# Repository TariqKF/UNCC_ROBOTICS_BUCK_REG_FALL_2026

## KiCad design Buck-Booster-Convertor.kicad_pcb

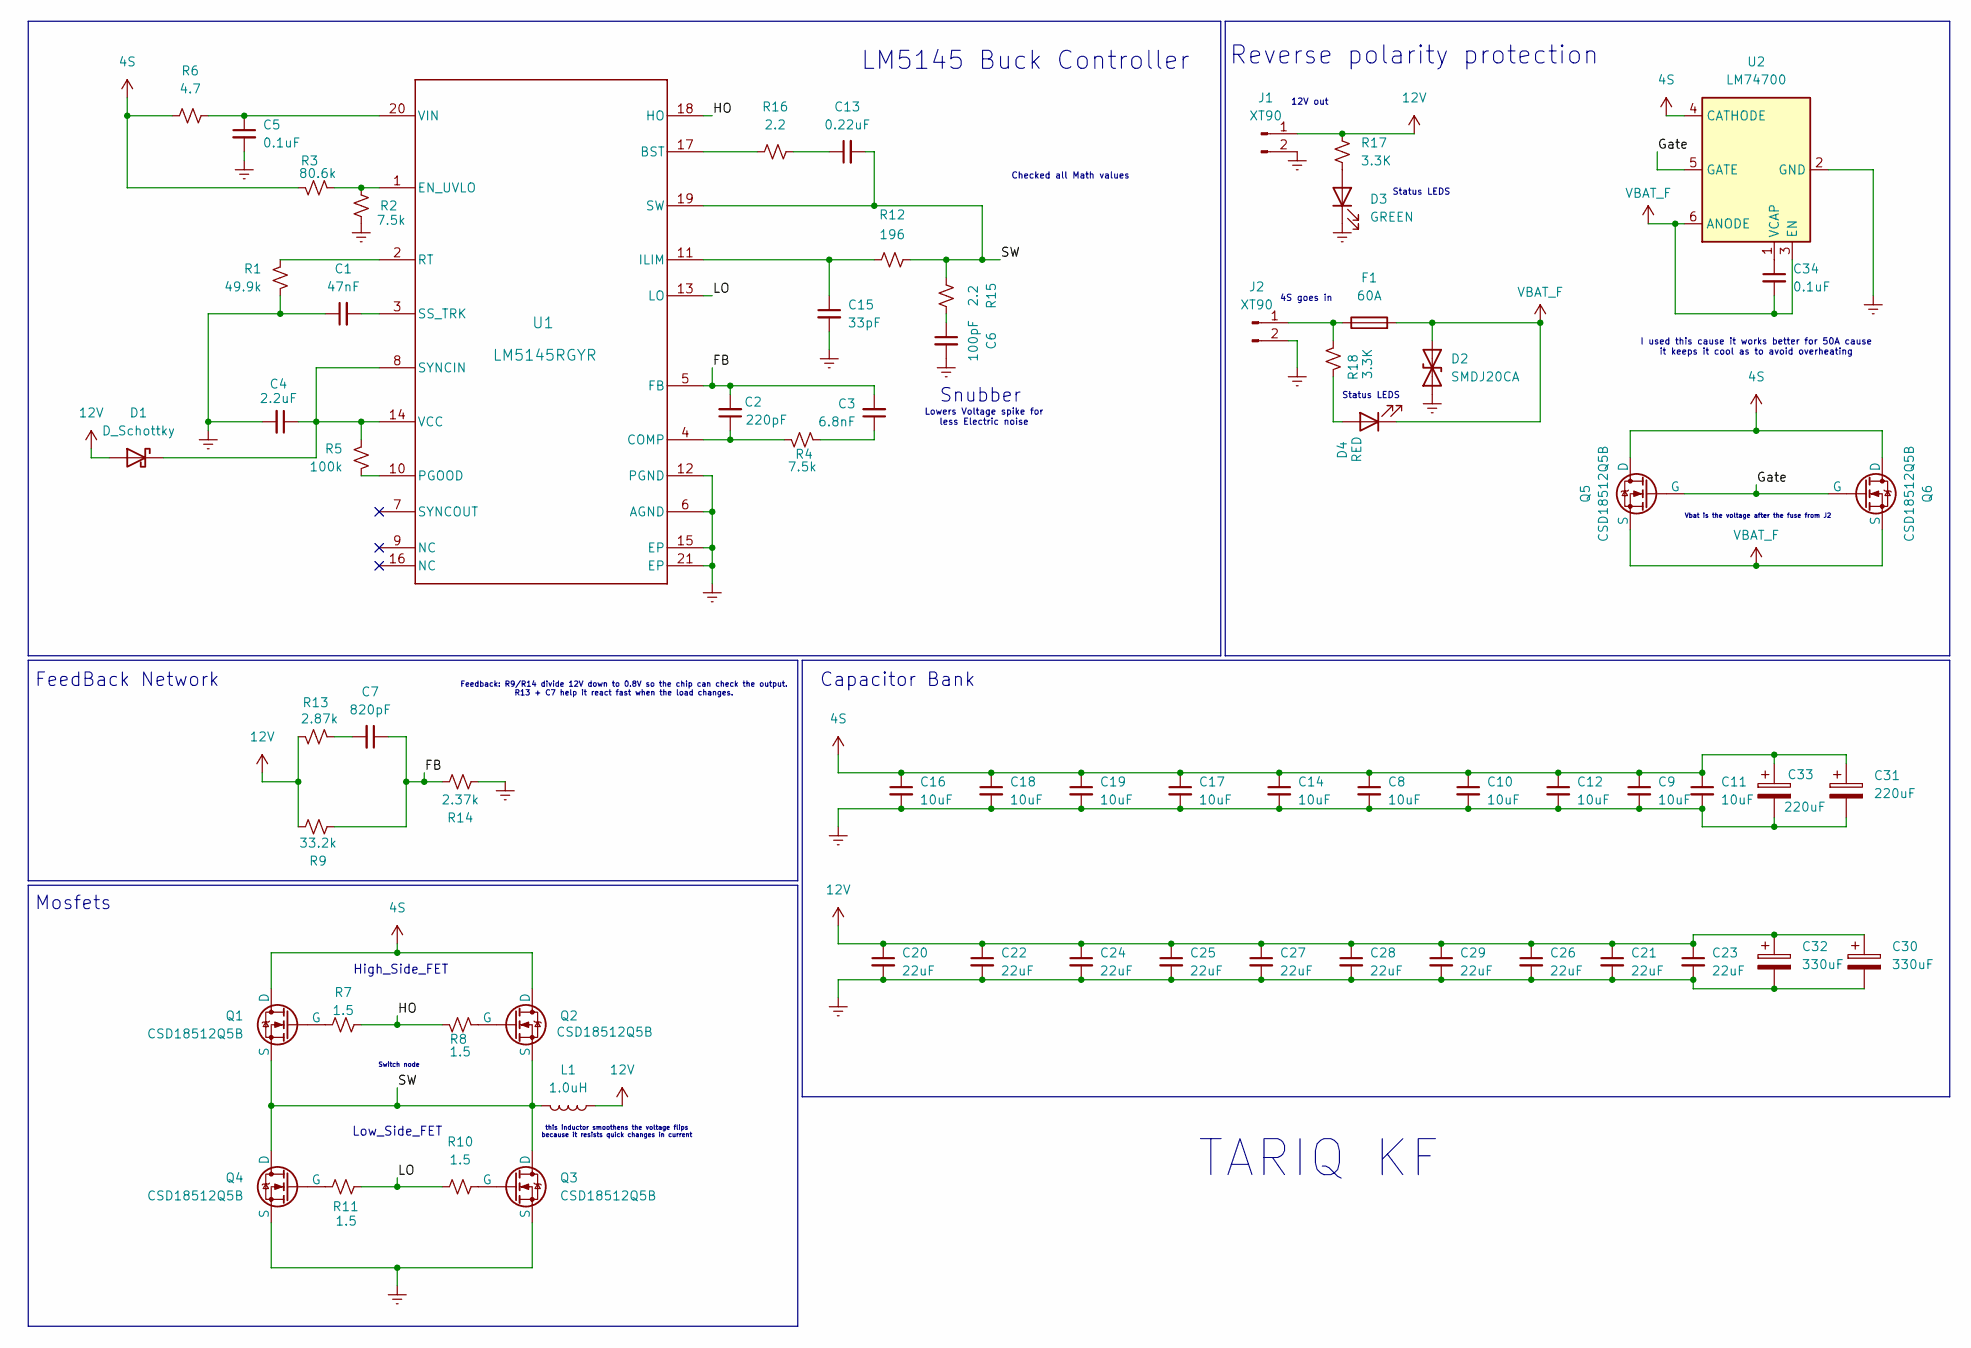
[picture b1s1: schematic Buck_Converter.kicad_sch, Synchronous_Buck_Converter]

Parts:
C1: 47nF; C_0402_1005Metric_Pad0.74x0.62mm_HandSolder
C2: 220pF; C_0402_1005Metric_Pad0.74x0.62mm_HandSolder
C3: 6.8nF; C_0402_1005Metric_Pad0.74x0.62mm_HandSolder
C4: 2.2uF; C_0603_1608Metric_Pad1.08x0.95mm_HandSolder
C5, C34: 0.1uF; C_0402_1005Metric_Pad0.74x0.62mm_HandSolder
C6: 100pF; C_0402_1005Metric_Pad0.74x0.62mm_HandSolder
C7: 820pF; C_0402_1005Metric_Pad0.74x0.62mm_HandSolder
C8, C9, C10, C11, C12, C14, C16, C17, C18, C19: 10uF; C_1210_3225Metric_Pad1.33x2.70mm_HandSolder
C13: 0.22uF; C_0603_1608Metric_Pad1.08x0.95mm_HandSolder
C15: 33pF; C_0402_1005Metric_Pad0.74x0.62mm_HandSolder
C20, C21, C22, C23, C24, C25, C26, C27, C28, C29: 22uF; C_1210_3225Metric_Pad1.33x2.70mm_HandSolder
C30, C32: 330uF; CP_Elec_10x12.6
C31, C33: 220uF; CP_Elec_8x10.5
D1: D_Schottky; D_SOD-123
D2: SMDJ20CA; D_SMC
D3: GREEN; LED_0603_1608Metric_Pad1.05x0.95mm_HandSolder
D4: RED; LED_0603_1608Metric_Pad1.05x0.95mm_HandSolder
F1: 60A; Fuseholder_Blade_ATO_Keystone_3560
J1, J2: XT90; AMASS_XT90PW-M_1x02_P10.90mm_Horizontal
L1: 1.0uH; L_Vishay_IHLP-6767
Q1, Q2, Q3, Q4, Q5, Q6: CSD18512Q5B; CSD18512Q5B_VSONP-8-1EP_5x6_P1.27mm_1D-2G-3S
R1: 49.9k; R_0402_1005Metric_Pad0.72x0.64mm_HandSolder
R2, R4: 7.5k; R_0402_1005Metric_Pad0.72x0.64mm_HandSolder
R3: 80.6k; R_0402_1005Metric_Pad0.72x0.64mm_HandSolder
R5: 100k; R_0402_1005Metric_Pad0.72x0.64mm_HandSolder
R6: 4.7; R_0402_1005Metric_Pad0.72x0.64mm_HandSolder
R7, R8, R10, R11: 1.5; R_0402_1005Metric_Pad0.72x0.64mm_HandSolder
R9: 33.2k; R_0402_1005Metric_Pad0.72x0.64mm_HandSolder
R12: 196; R_0402_1005Metric_Pad0.72x0.64mm_HandSolder
R13: 2.87k; R_0402_1005Metric_Pad0.72x0.64mm_HandSolder
R14: 2.37k; R_0402_1005Metric_Pad0.72x0.64mm_HandSolder
R15, R16: 2.2; R_0402_1005Metric_Pad0.72x0.64mm_HandSolder
R17, R18: 3.3K; R_0402_1005Metric_Pad0.72x0.64mm_HandSolder
U1: LM5145RGYR; Texas_RGY_R-PVQFN-N20_EP2.05x3.05mm_ThermalVias
U2: LM74700; SOT-23-6

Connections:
4S: C8.1, C9.1, C10.1, C11.1, C12.1, C14.1, C16.1, C17.1, C18.1, C19.1, C31.1, C33.1, Q1.1 (D), Q2.1 (D), Q5.1 (D), Q6.1 (D), R3.2, R6.1, U2.4 (CATHODE)
12V: C20.1, C21.1, C22.1, C23.1, C24.1, C25.1, C26.1, C27.1, C28.1, C29.1, C30.1, C32.1, D1.2 (A), J1.1, L1.1, R9.2, R13.1, R17.2
/Buck_Converter/FB: C2.2, C3.2, C7.1, R9.1, R14.2, U1.5 (FB)
/Buck_Converter/Gate: Q5.2 (G), Q6.2 (G), U2.5 (GATE)
/Buck_Converter/HO: R7.2, R8.1, U1.18 (HO)
/Buck_Converter/LO: R10.1, R11.2, U1.13 (LO)
/Buck_Converter/SW: C13.2, L1.2, Q1.3 (S), Q2.3 (S), Q3.1 (D), Q4.1 (D), R12.2, R15.1, U1.19 (SW)
GNDREF: C1.1, C4.2, C5.2, C6.2, C8.2, C9.2, C10.2, C11.2, C12.2, C14.2, C15.2, C16.2, C17.2, C18.2, C19.2, C20.2, C21.2, C22.2, C23.2, C24.2, C25.2, C26.2, C27.2, C28.2, C29.2, C30.2, C31.2, C32.2, C33.2, D2.1 (A1), D3.1 (K), J1.2, J2.2, Q3.3 (S), Q4.3 (S), R1.2, R2.1, R14.1, U1.6 (AGND), U1.12 (PGND), U1.15 (EP), U1.21 (EP), U2.2 (GND)
unnamed: C3.1, R4.2
unnamed: C6.1, R15.2
unnamed: C7.2, R13.2
unnamed: C13.1, R16.2
unnamed: C4.1, D1.1 (K), R5.1, U1.8 (SYNCIN), U1.14 (VCC)
unnamed: D3.2 (A), R17.1
unnamed: D4.2 (A), R18.1
unnamed: F1.1, J2.1, R18.2
unnamed: Q1.2 (G), R7.1
unnamed: Q2.2 (G), R8.2
unnamed: Q3.2 (G), R10.2
unnamed: Q4.2 (G), R11.1
unnamed: R16.1, U1.17 (BST)
unnamed: C2.1, R4.1, U1.4 (COMP)
unnamed: R2.2, R3.1, U1.1 (EN_UVLO)
unnamed: C15.1, R12.1, U1.11 (ILIM)
unnamed: R5.2, U1.10 (PGOOD)
unnamed: R1.1, U1.2 (RT)
unnamed: C1.2, U1.3 (SS_TRK)
unnamed: C5.1, R6.2, U1.20 (VIN)
unnamed: C34.1, U2.1 (VCAP)
VBAT_F: C34.2, D2.2 (A2), D4.1 (K), F1.2, Q5.3 (S), Q6.3 (S), U2.3 (EN), U2.6 (ANODE)

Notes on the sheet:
Status LEDS
Reverse polarity protection
4S goes in
Lowers Voltage spike for less Electric noise
FeedBack Network
12V out
Switch node
Mosfets
High_Side_FET
TARIQ KF
this inductor smoothens the voltage flips because it resists quick changes in current
Vbat is the voltage after the fuse from J2
Capacitor Bank
I used this cause it works better for 50A cause it keeps it cool as to avoid overheating
Checked all Math values
Feedback: R9/R14 divide 12V down to 0.8V so the chip can check the output. R13 + C7 help it react fast when the load changes.
Snubber
Low_Side_FET
LM5145 Buck Controller

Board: 2 copper layers, 68 parts (0 on the bottom side), 30 nets, no tracks yet.
